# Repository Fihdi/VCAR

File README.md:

# 8hp Voltage Controlled Attack Release / Slew Rate Limiter

VCAR is based on the Serge Dual Universal Slope Generator (DUSG). In Envelope mode, VCAR acts as an Attack-Release Envelope. With the LOOP switch engaged, the AR Envelope cycles indefinitely, allowing for VCO or LFO usage depending on the rate set by the Attack and Release settings. The looping can be stopped with an active Gate being present at the LOOP inhibit input. In Slew mode the output follows the input with a limited slew rate.

Use cases include Envelope Follower, Gate Delay, LFO/VCO, VCA, Wave Shaper, AR-Envelope, AHR-Envelope, Gate to Trigger Converter.

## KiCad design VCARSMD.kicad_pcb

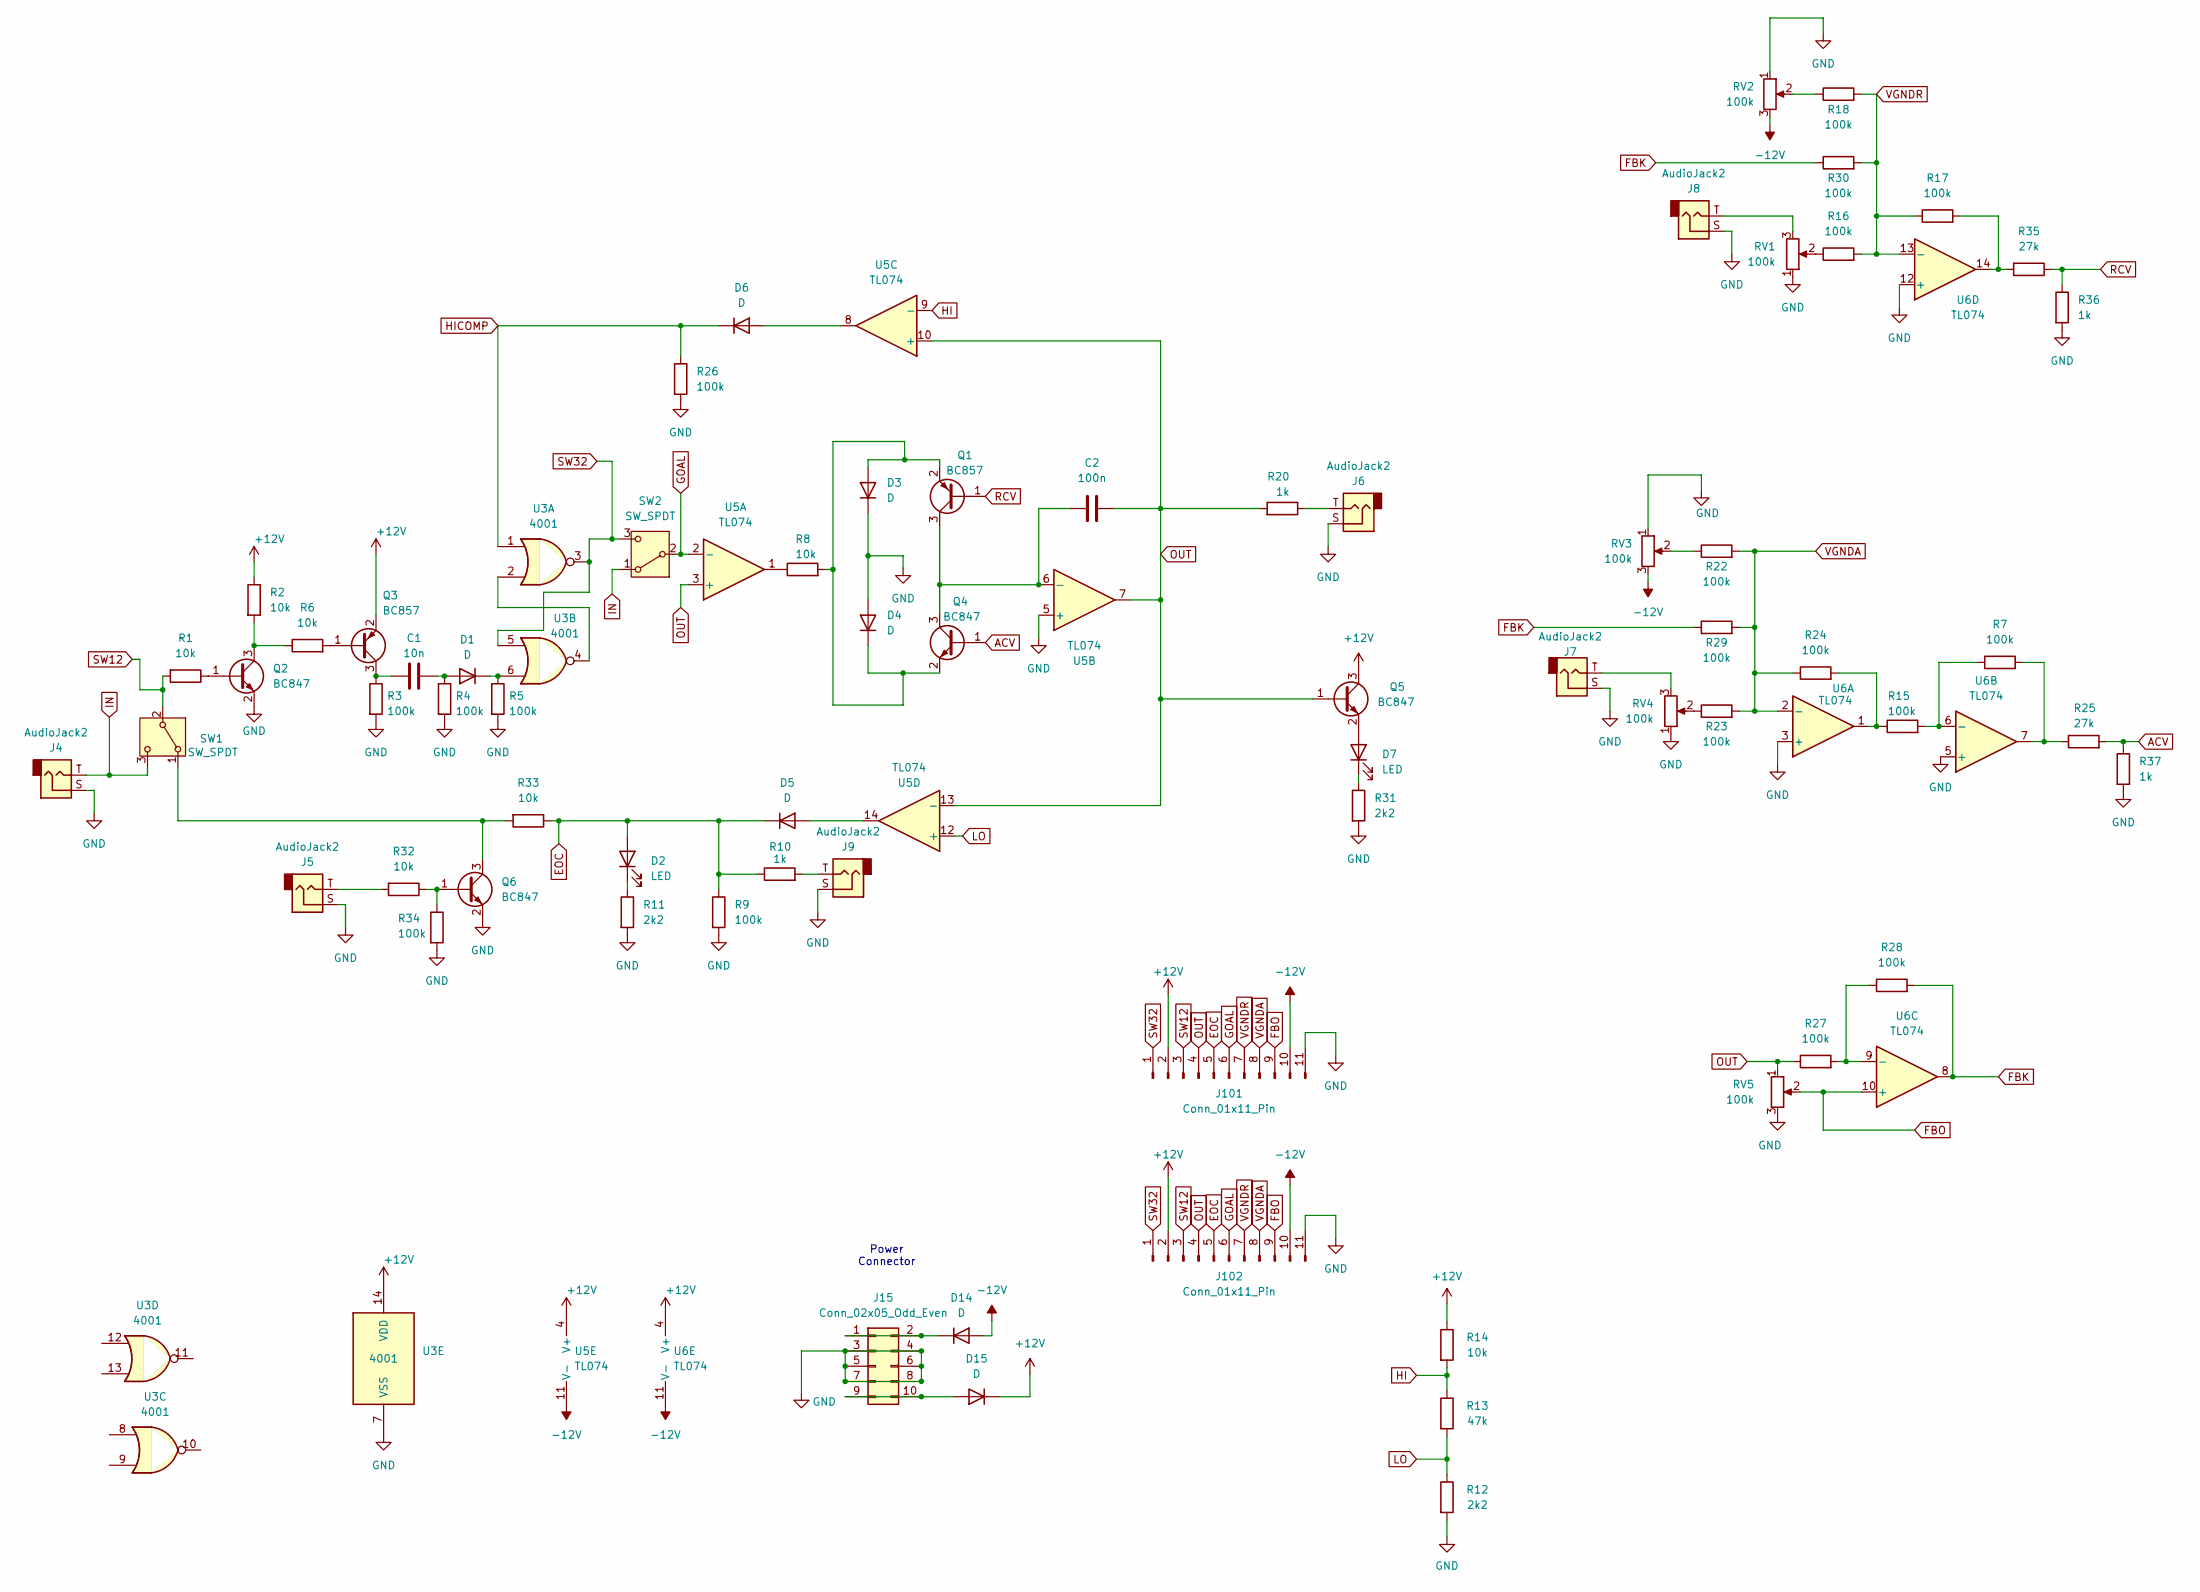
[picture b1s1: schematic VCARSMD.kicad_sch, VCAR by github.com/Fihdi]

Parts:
C1: 10n; C_1206_3216Metric
C2: 100n; C_1206_3216Metric
D1, D3, D4, D5, D6, D14, D15: D; D_SOD-323_HandSoldering
D2, D7: LED; LED_D3.0mm
J4, J5, J6, J7, J8, J9: AudioJack2; MonoTRS
J15: Conn_02x05_Odd_Even; IDC-Header_2x05_P2.54mm_Vertical
J101, J102: Conn_01x11_Pin; PinSocket_1x11_P2.54mm_Vertical
Q1, Q3: BC857; SOT-23
Q2, Q4, Q5, Q6: BC847; SOT-23
R1, R2, R6, R8, R14, R32, R33: 10k; R_1206_3216Metric
R3, R4, R5, R7, R9, R15, R16, R17, R18, R22, R23, R24, R26, R27, R28, R29, R30, R34: 100k; R_1206_3216Metric
R10, R20, R36, R37: 1k; R_1206_3216Metric
R11, R12, R31: 2k2; R_1206_3216Metric
R13: 47k; R_1206_3216Metric
R25, R35: 27k; R_1206_3216Metric
RV1, RV2, RV3, RV4, RV5: 100k; Potentiometer_Alpha_RD901F-40-00D_Single_Vertical
SW1, SW2: SW_SPDT; Switch
U3: 4001; SO-14_3.9x8.65mm_P1.27mm
U5, U6: TL074; SO-14_3.9x8.65mm_P1.27mm

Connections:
+12V: D15.1 (K), J101.2, J102.2, Q3.2 (E), Q5.3 (C), R2.1, R14.1, U3.14 (VDD), U5.4 (V+), U6.4 (V+)
-12V: D14.2 (A), J101.10, J102.10, RV2.3, RV3.3, U5.11 (V-), U6.11 (V-)
ACV: Q4.1 (B), R25.2, R37.1
EOC: D2.2 (A), D5.1 (K), J101.5, J102.5, R9.1, R10.1, R33.1
FBK: R28.2, R29.1, R30.1, U6.8
FBO: J101.9, J102.9, RV5.2, U6.10 (+)
GND: D3.1 (K), D4.2 (A), J4.S, J5.S, J6.S, J7.S, J8.S, J9.S, J15.3, J15.4, J15.5, J15.6, J15.7, J15.8, J101.11, J102.11, Q2.2 (E), Q6.2 (E), R3.2, R4.2, R5.2, R9.2, R11.2, R12.2, R26.2, R31.2, R34.2, R36.2, R37.2, RV1.1, RV2.1, RV3.1, RV4.1, RV5.3, U3.7 (VSS), U5.5 (+), U6.3 (+), U6.5 (+), U6.12 (+)
GOAL: J101.6, J102.6, SW2.2 (B), U5.2 (-)
HI: R13.1, R14.2, U5.9 (-)
HICOMP: D6.1 (K), R26.1, U3.1
IN: J4.T, SW1.3 (C), SW2.1 (A)
LO: R12.1, R13.2, U5.12 (+)
unnamed: C1.2, D1.2 (A), R4.1
unnamed: D1.1 (K), R5.1, U3.6
unnamed: D2.1 (K), R11.1
unnamed: D3.2 (A), D4.1 (K), Q1.2 (E), Q4.2 (E), R8.2
unnamed: D5.2 (A), U5.14
unnamed: D6.2 (A), U5.8
unnamed: D7.2 (A), Q5.2 (E)
unnamed: D7.1 (K), R31.1
unnamed: D14.1 (K), J15.1, J15.2
unnamed: D15.2 (A), J15.9, J15.10
unnamed: J5.T, R32.2
unnamed: J6.T, R20.1
unnamed: J7.T, RV4.3
unnamed: J8.T, RV1.3
unnamed: J9.T, R10.2
unnamed: C2.1, Q1.3 (C), Q4.3 (C), U5.6 (-)
unnamed: Q2.1 (B), R1.1
unnamed: Q2.3 (C), R2.2, R6.1
unnamed: Q3.1 (B), R6.2
unnamed: C1.1, Q3.3 (C), R3.1
unnamed: Q6.1 (B), R32.1, R34.1
unnamed: Q6.3 (C), R33.2, SW1.1 (A)
unnamed: R8.1, U5.1
unnamed: R15.1, R24.2, U6.1
unnamed: R16.1, RV1.2
unnamed: R17.2, R35.2, U6.14
unnamed: R18.1, RV2.2
unnamed: R22.1, RV3.2
unnamed: R23.1, RV4.2
unnamed: R7.2, R25.1, U6.7
unnamed: U3.2, U3.4
unnamed: R7.1, R15.2, U6.6 (-)
unnamed: R27.2, R28.1, U6.9 (-)
OUT: C2.2, J101.4, J102.4, Q5.1 (B), R20.2, R27.1, RV5.1, U5.3 (+), U5.7, U5.10 (+), U5.13 (-)
RCV: Q1.1 (B), R35.1, R36.1
SW12: J101.3, J102.3, R1.2, SW1.2 (B)
SW32: J101.1, J102.1, SW2.3 (C), U3.3, U3.5
VGNDA: J101.8, J102.8, R22.2, R23.2, R24.1, R29.2, U6.2 (-)
VGNDR: J101.7, J102.7, R16.2, R17.1, R18.2, R30.2, U6.13 (-)

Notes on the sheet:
Power Connector

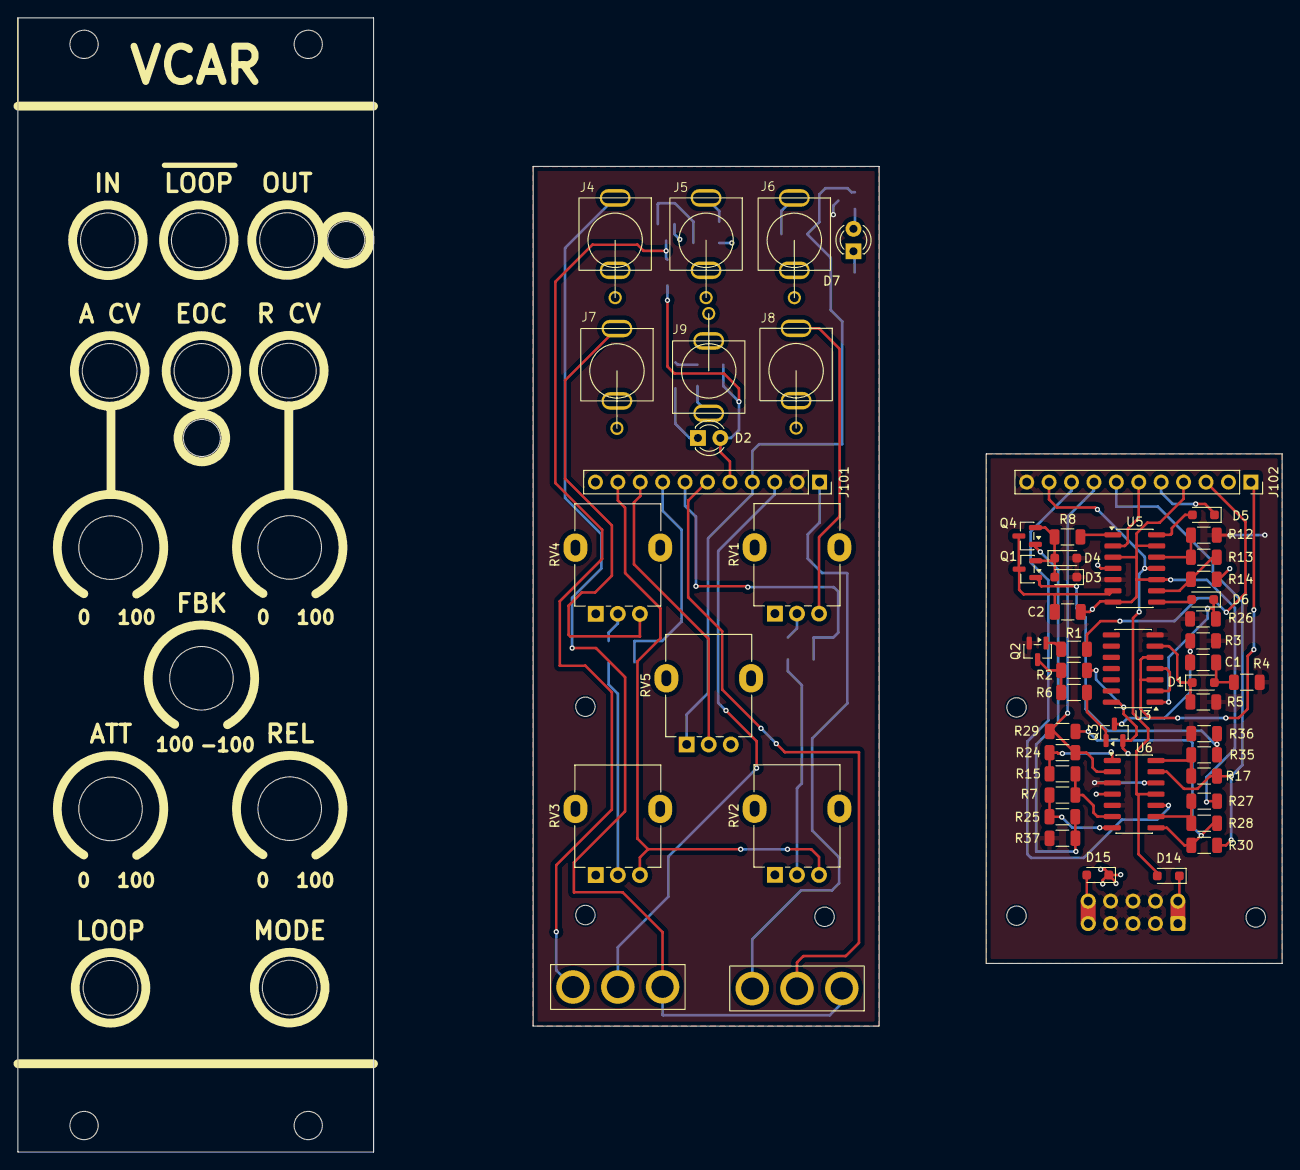
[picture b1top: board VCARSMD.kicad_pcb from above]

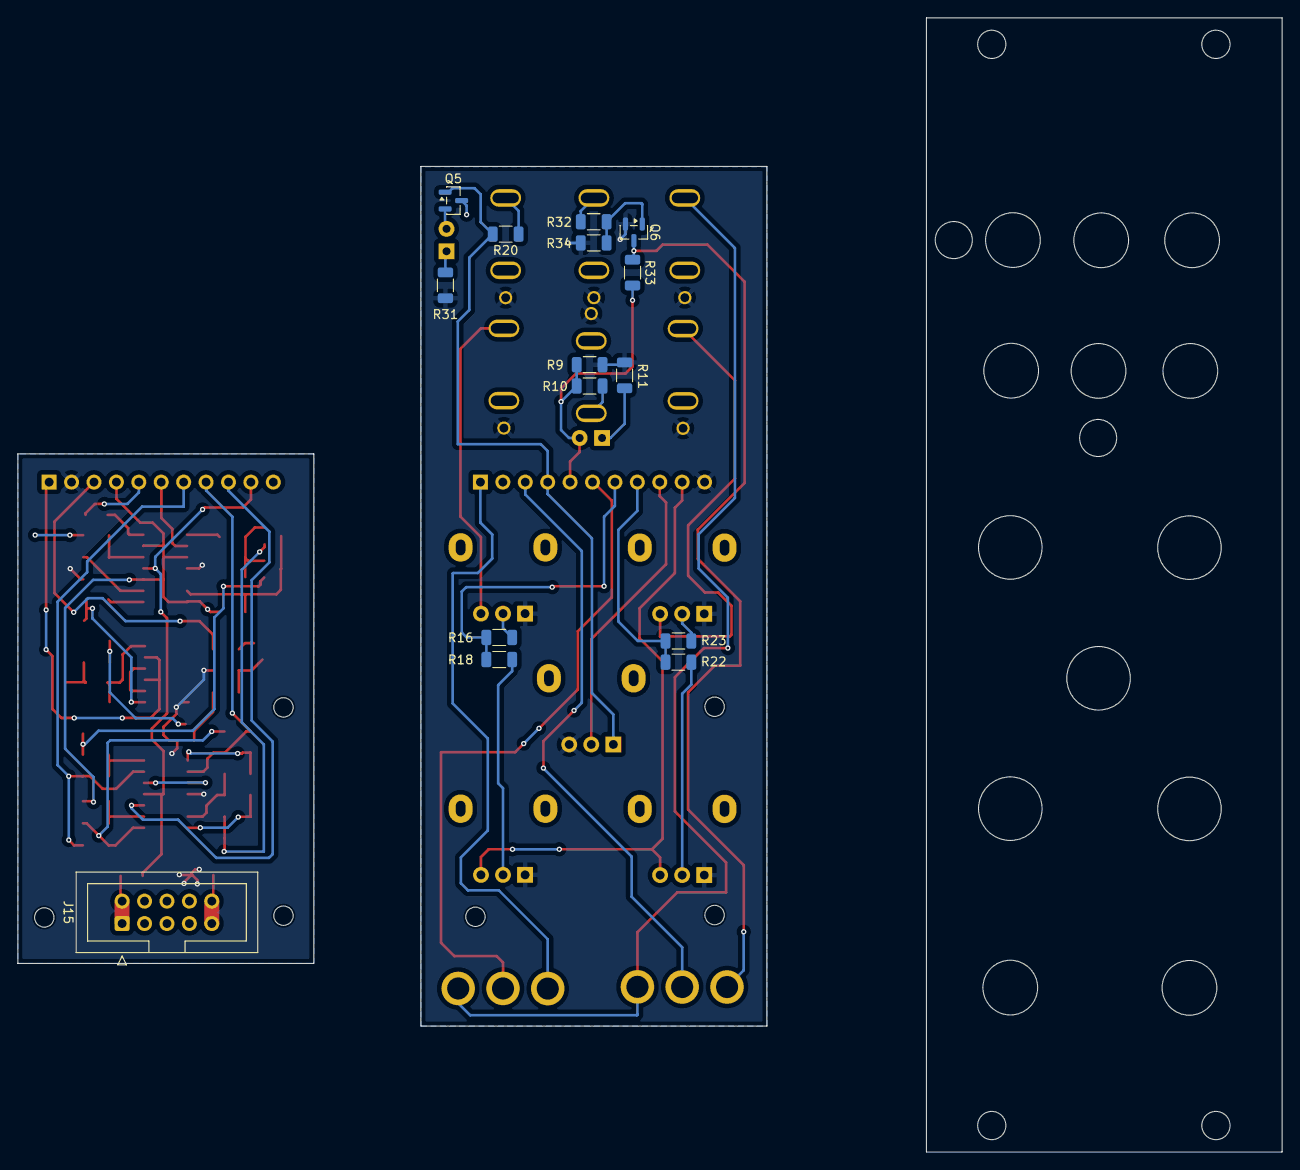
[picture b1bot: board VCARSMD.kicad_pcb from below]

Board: 2 copper layers, 143.2 x 128.5 mm, 71 parts (15 on the bottom side), 51 nets.

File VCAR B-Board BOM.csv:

"Reference","Qty","Value","DNP","Exclude from BOM","Exclude from Board","Footprint","Datasheet"
"C1","1","10n","","","","Capacitor_SMD:C_1206_3216Metric","~"
"C2","1","100n","","","","Capacitor_SMD:C_1206_3216Metric","~"
"D1,D3,D4,D5,D6,D14,D15","7","D","","","","Diode_SMD:D_SOD-323_HandSoldering","~"
"J15","1","Conn_02x05_Odd_Even","","","","Connector_IDC:IDC-Header_2x05_P2.54mm_Vertical","~"
"J102","1","Conn_01x11_Pin","","","","Connector_PinSocket_2.54mm:PinSocket_1x11_P2.54mm_Vertical","~"
"Q1,Q3","2","BC857","","","","Package_TO_SOT_SMD:SOT-23","https://www.onsemi.com/pub/Collateral/BC860-D.pdf"
"Q2,Q4","2","BC847","","","","Package_TO_SOT_SMD:SOT-23","http://www.infineon.com/dgdl/Infineon-BC847SERIES_BC848SERIE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"
"R1,R2,R6,R8,R14","5","10k","","","","Resistor_SMD:R_1206_3216Metric","~"
"R3,R4,R5,R7,R15,R17,R24,R26,R27,R28,R29,R30","12","100k","","","","Resistor_SMD:R_1206_3216Metric","~"
"R12","1","2k2","","","","Resistor_SMD:R_1206_3216Metric","~"
"R13","1","47k","","","","Resistor_SMD:R_1206_3216Metric","~"
"R25,R35","2","27k","","","","Resistor_SMD:R_1206_3216Metric","~"
"R36,R37","2","1k","","","","Resistor_SMD:R_1206_3216Metric","~"
"U3","1","4001","","","","Package_SO:SO-14_3.9x8.65mm_P1.27mm","http://www.intersil.com/content/dam/Intersil/documents/cd40/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"
"U5,U6","2","TL074","","","","Package_SO:SO-14_3.9x8.65mm_P1.27mm","http://www.ti.com/lit/ds/symlink/tl071.pdf"
